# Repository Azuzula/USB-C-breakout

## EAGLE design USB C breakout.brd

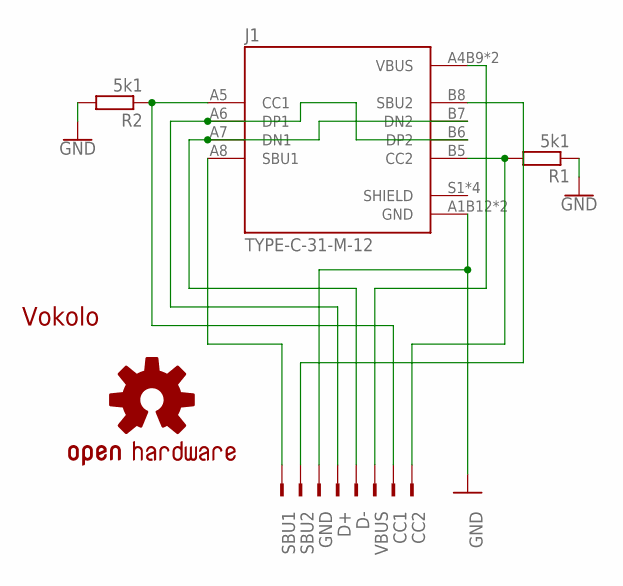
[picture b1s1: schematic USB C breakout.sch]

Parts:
J1: TYPE-C-31-M-12; HRO_TYPE-C-31-M-12
LOGO1: OSHW-LOGOS; OSHW-LOGO-S
R1, R2: 5k1; R0603
U$1: LOGO_VOKOLO12MM; LOGO_VOKOLO_9,8MM
X1: TSW-108-07-G-S; TSW-108-XX-G-S

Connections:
CC1: J1.A5 (CC1), R2.1, X1.2
CC2: J1.B5 (CC2), R1.2, X1.1
D+: J1.A6 (DP1), J1.B6 (DP2), X1.5
D-: J1.A7 (DN1), J1.B7 (DN2), X1.4
GND: J1.A1B12 (GND), J1.B1A12 (GND), R1.1, R2.2, X1.6
SBU1: J1.A8 (SBU1), X1.8
SBU2: J1.B8 (SBU2), X1.7
VBUS: J1.A4B9 (VBUS), J1.B4A9 (VBUS), X1.3

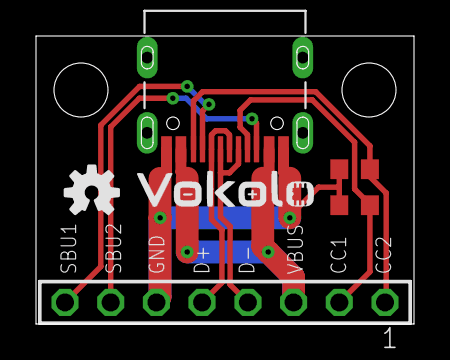
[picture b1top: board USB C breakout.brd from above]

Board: 2 copper layers, 21.0 x 16.0 mm, 6 parts (0 on the bottom side), 8 nets.

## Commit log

2023-10-09 Add files via upload
    New version USB-C breakout board.

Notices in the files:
parts and their libraries:
SparkFun-Aesthetics: Licensing: Creative Commons ShareAlike 4.0 International - https://creativecommons.org/licenses/by-sa/4.0
